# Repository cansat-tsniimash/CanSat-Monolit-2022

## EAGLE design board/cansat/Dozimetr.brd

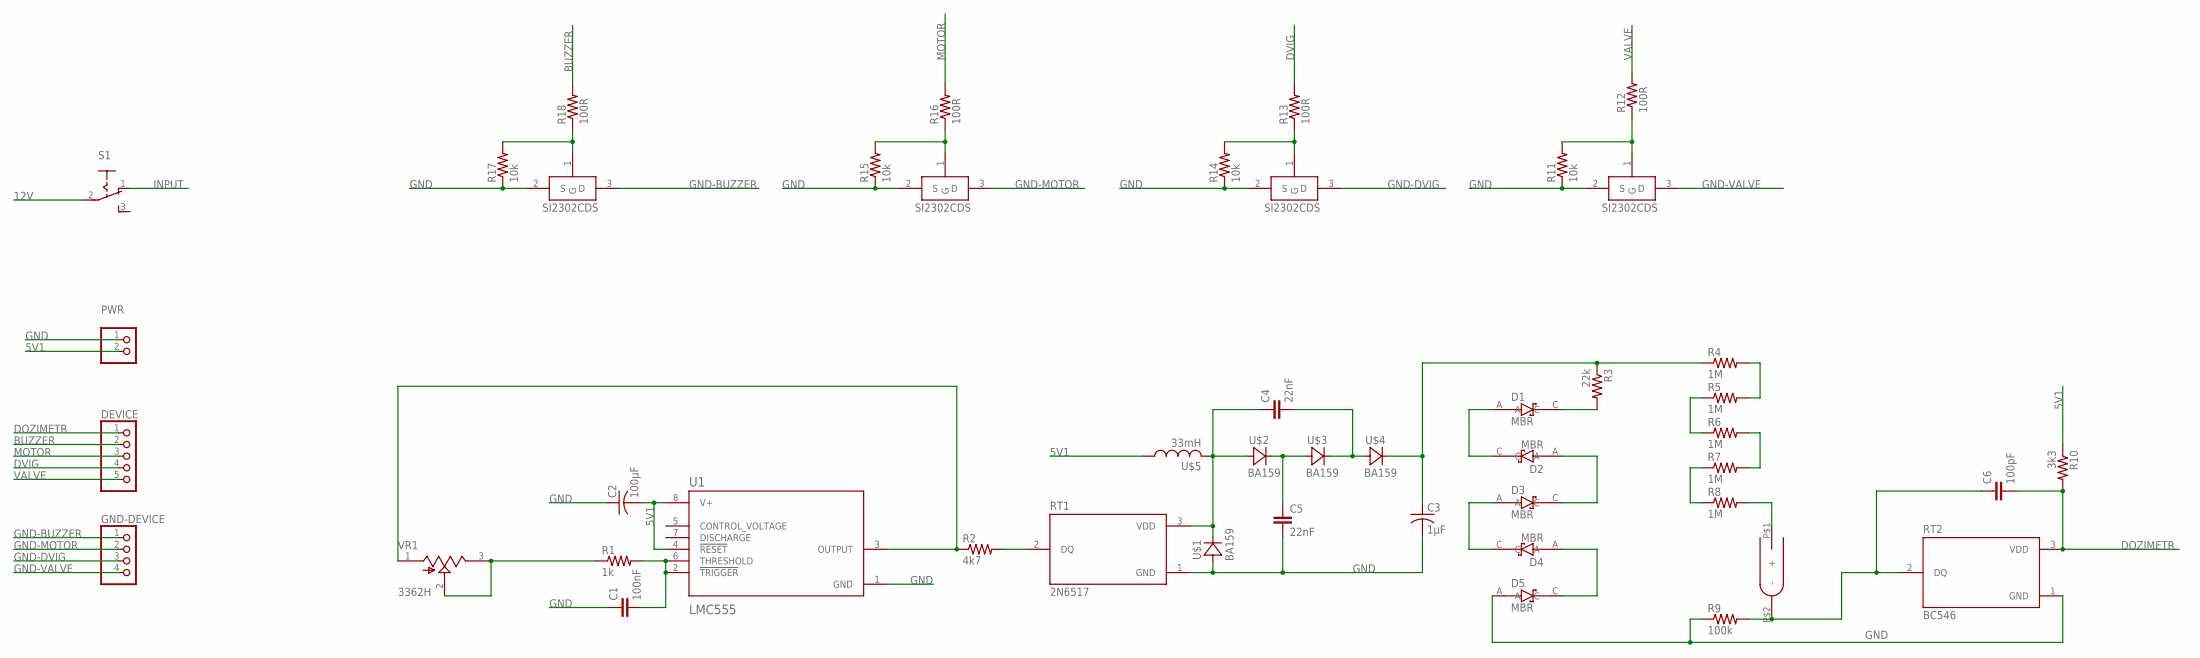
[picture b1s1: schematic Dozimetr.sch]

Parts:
C1: 100nF; C0603
C2: 100μF; ECAP100-CMD
C3: 1μF; ECAP1MK
C4, C5: 22nF; C1210
C6: 100pF; C0603
D1, D2, D3, D4, D5: MBR; SOD123
DEVICE: PINHD-1X5; 1X05
DOSE: DOSIM_SBM20-1
GND-DEVICE: PINHD-1X4; 1X04
PWR: PINHD-1X2; 1X02
R1: 1k; R0603
R2: 4k7; R0603
R3: 22k; R0603
R4, R5, R6, R7, R8: 1M; R0603
R9: 100k; R0603
R10: 3k3; R0603
R11, R14, R15, R17: 10k; R0603
R12, R13, R16, R18: 100R; R0603
RT1: 2N6517; TO92/TO226
RT2: BC546; TO92/TO226
S1: SWITCH-BIG
SI2302-1, SI2302-2, SI2302-3, SI2302-4: SI2302CDS; SOT23-3
U1: LMC555; SOIC127P599X175-8N
U$1, U$2, U$3, U$4: BA159
U$5: 33mH; RCH114NP_-
VR1: 3362H; TRIM_3362H-1-502LF

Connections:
5V1: C2.P$2 (2), PWR.2, R10.1, U1.4 (!RESET!), U1.8 (V+), U$5.P$1 (1)
12V: S1.2
BUZZER: DEVICE.2, R18.2
DOZIMETR: C6.2, DEVICE.1, R10.2, RT2.3 (VDD)
DVIG: DEVICE.4, R13.2
GND: C1.1, C2.P$1 (1), C3.P$2 (2), C5.2, D5.A, PWR.1, R9.1, R11.1, R14.1, R15.1, R17.1, RT1.1 (GND), RT2.1 (GND), SI2302-1.2 (S), SI2302-2.2 (S), SI2302-3.2 (S), SI2302-4.2 (S), U1.1 (GND), U$1.P$1 (A)
GND-BUZZER: GND-DEVICE.1, SI2302-1.3 (D)
GND-DVIG: GND-DEVICE.3, SI2302-3.3 (D)
GND-MOTOR: GND-DEVICE.2, SI2302-2.3 (D)
GND-VALVE: GND-DEVICE.4, SI2302-4.3 (D)
INPUT: S1.1 (O)
MOTOR: DEVICE.3, R16.2
unnamed: C1.2, R1.2, U1.2 (!TRIGGER!), U1.6 (THRESHOLD)
unnamed: R1.1, VR1.2 (WIPER), VR1.3 (CW)
unnamed: R2.1, U1.3 (OUTPUT), VR1.1 (CCW)
unnamed: C4.1, RT1.3 (VDD), U$1.P$2 (C), U$2.P$1 (A), U$5.P$2 (2)
unnamed: R2.2, RT1.2 (DQ)
unnamed: C5.1, U$2.P$2 (C), U$3.P$1 (A)
unnamed: C4.2, U$3.P$2 (C), U$4.P$1 (A)
unnamed: C3.P$1 (1), R3.1, R4.1, U$4.P$2 (C)
unnamed: D4.A, D5.C
unnamed: D3.A, D4.C
unnamed: D2.A, D3.C
unnamed: D1.A, D2.C
unnamed: D1.C, R3.2
unnamed: R4.2, R5.2
unnamed: R5.1, R6.1
unnamed: R6.2, R7.2
unnamed: R7.1, R8.1
unnamed: DOSE.P$1 (+), R8.2
unnamed: C6.1, DOSE.P$2 (-), R9.2, RT2.2 (DQ)
unnamed: R17.2, R18.1, SI2302-1.1 (G)
unnamed: R15.2, R16.1, SI2302-2.1 (G)
unnamed: R13.1, R14.2, SI2302-3.1 (G)
unnamed: R11.2, R12.1, SI2302-4.1 (G)
VALVE: DEVICE.5, R12.2

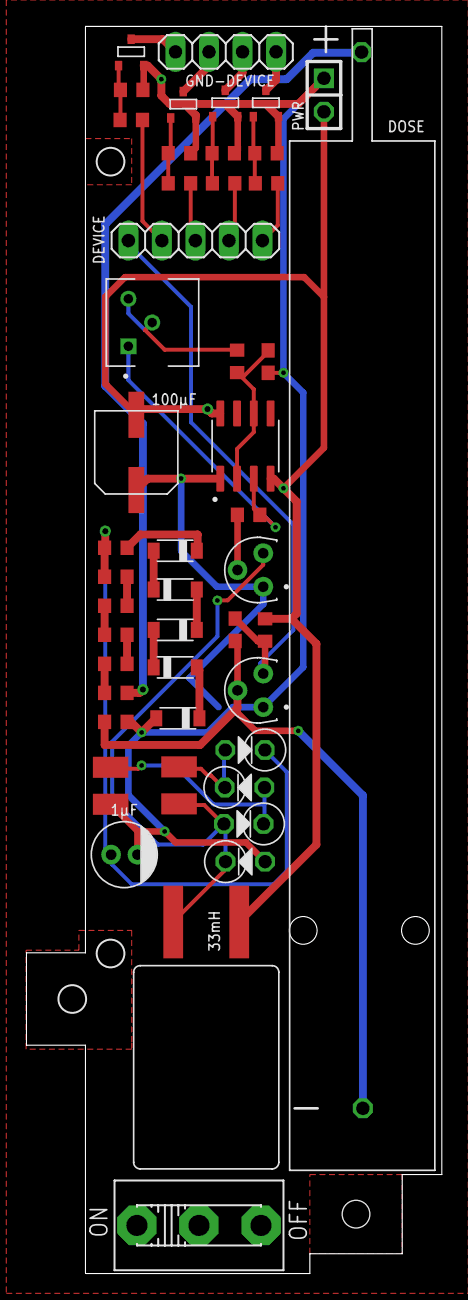
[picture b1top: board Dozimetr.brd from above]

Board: 2 copper layers, 31.5 x 94.5 mm, 47 parts (0 on the bottom side), 34 nets.

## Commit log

2022-02-16 Залиты все модели
2022-02-16 Добавлены файлы проектов для BME280, mems, photores
2022-02-23 закинули файлы гпс в гит
2022-02-23 Загружена схема дозиметра
2022-02-23 Добавлен большой переключатель
2022-02-23 довели до нормы гпс
2022-02-26 схема дозиметра разведена
2022-02-26 Расставлены подписи на плате
2022-03-02 добавил gitignore シ
2022-03-02 заигнорил файлы папки дебуг
2022-03-02 гит игнор :)
2022-03-02 зачистили неудалившиеся дебаги
2022-03-02 зачистили неудалившиеся сеттингс
2022-03-02 просто добил файлы :)
2022-03-02 обновили библиотеку
2022-03-06 пытаемся сделать картинки в рпз
2022-03-06 Добавлены картинки сборок
2022-03-19 запилили драйвер на фоторезистор
2022-03-19 перешёл на ласт коммит либ-цниимаша
2022-03-20 Добавлены все файлы по ЗС
2022-03-26 пилили драйвер на бмеху
2022-03-28 сабмодули на относительных путях
2022-05-02 Подушка безопасности
2022-05-02 Новый либ-цниимаш
2022-05-04 Радио работает
2022-05-04 Апп_майн работы с радио
2022-05-04 Датчики работают, А радио нет
2022-05-07 Кодик для шакала на Андрее
2022-05-07 Вкрутили фоторез
2022-05-08 ГПС вкручен, но не ловит данные (надо тестить) и выводит нули
2022-05-11 ЛИСМ вкручен и проверен
2022-05-21 Плата дозиметра готова
2022-06-08 Закончены состояния, написаны различные ф-ии
2022-06-08 Вкручен проверен ДС18, начаты состояния
2022-06-08 Написана система безопасности для СД-карты
2022-06-09 Достигнут компромисс с конструкторами по поводу пинов
2022-06-11 ОТЛАДКА
2022-06-15 ПОчинка кнопки
2022-06-15 ФИКС БАГИ С ИНЕРЦИАЛКОЙ + ПРОВЕРКА И ФИКС СОСТОЯНИЙ
2022-06-29 Норм рабочая версия, надо поймать ГПС
2022-06-29 Оказалось, что проблема ГПС - в антенне, написаны косметические ф-ии
